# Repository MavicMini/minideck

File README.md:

# MiniDeck  

MiniDeck is a macropad that I have designed to have a lot of functionality in a fairly small package. I wanted to build in the ability to expand its functionalty from just being a macropad to a device which can be used to control smart home devices as well.  

## Features
- 11 Mechanical Switches
- EC11 rotary encoder with push button
- 0.91" 128x32 OLED display
- Sleek case with M3 heat set inserts

## To Do
- ✅ PCB design
- ✅ Case Design
- ✅ Basic KMK firmware
- ❌ Expanded KMK Firmware
- ❌ QMK firmware
- ❌ HomeAssistant integration

## Renders

## CAD Model
All parts are attatches with M3x6mm bolts to make it simple and they screw into 6 M3x4mm heatset inserts. This allows the PCB to be held down with 2 bolts and the case lid 4 bolts.  

The case is printed in two parts, the base and the lid.  

To have the logo stand out I want to have the logo and text be white, my printer only does one colour at a time though. So to achieve the two tone design I need to add a layer pause in the slicer to allow me to change filament during this point and then let it print the last 2 layers of text in white filament.

## PCB
Here is the schematic for the PCB, which were both made in KiCAD. The silkscreen logo was made in Adobe Illustrator.  
**PCB**  

**Schematic**  

## Firmware  
I am going to use KMK firmware to start off with as im more familiar with python so it should be easier to write. However, from the research I've done there are definetly benefits to using QMK, so in the future I might release a QMK firmware version as well.  

Below is a list of the features are currently in the firmware:  
- Rotary encoder changes master system volume
- OLED Displays current volume (Only Works if the volume is exclsivley changed from the MiniDeck)
- 11 Mechanical keys are macros

I plan to add more features and use some keys as modifer keys to extend the functionality of the MiniDeck.

## BOM  
- 11x Cherry MX Switches
- 11x DSA Keycaps
- 6x M3x4mm Heatset Inserts
- 6x M3*6mm Bolts
- 12x 1N4148 Diodes
- 1x 0.91" 128x32 OLED Display
- 1x EC11 Rotary Encoder
- 1x XIAO RP2040
- 1x Top Cover (3D Printed)
- 1x Bottom Case (3D Printed)

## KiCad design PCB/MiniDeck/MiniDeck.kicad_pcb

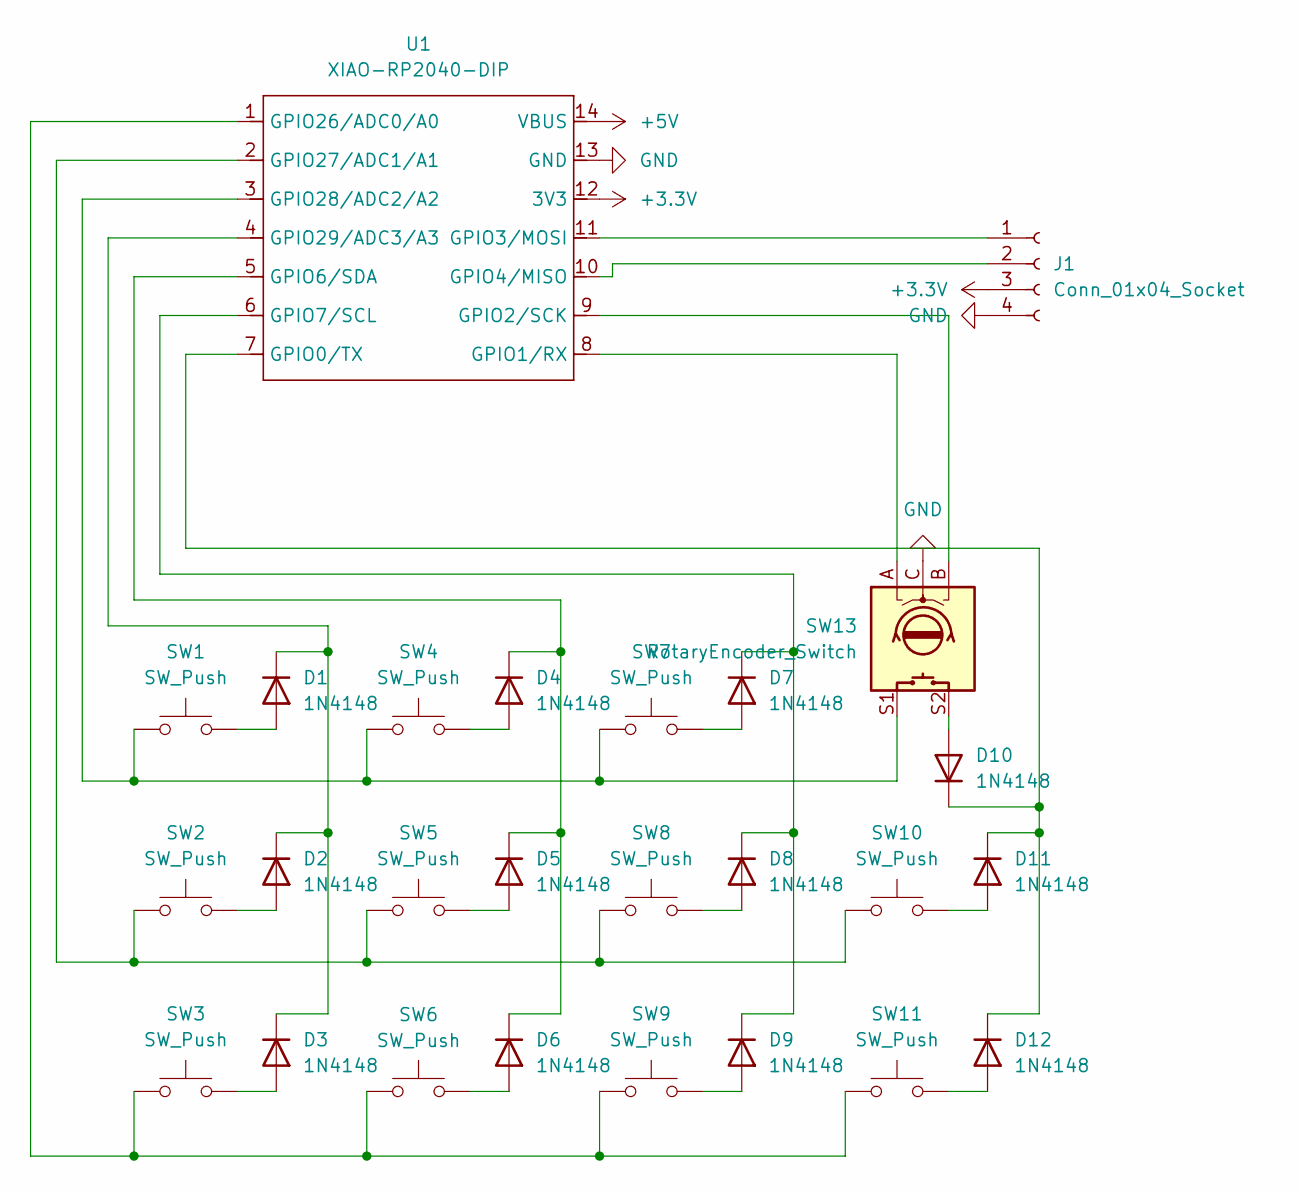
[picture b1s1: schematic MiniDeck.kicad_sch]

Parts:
D1, D2, D3, D4, D5, D6, D7, D8, D9, D10, D11, D12: 1N4148; D_DO-35_SOD27_P7.62mm_Horizontal
J1: Conn_01x04_Socket; PinHeader_1x04_P2.54mm-ce12909e-c1ba-0606-2421-5b6e827065f4
SW1, SW2, SW3, SW4, SW5, SW6, SW7, SW8, SW9, SW10, SW11: SW_Push; SW_Cherry_MX_1.00u_PCB-3D Model
SW13: RotaryEncoder_Switch; RotaryEncoder_Alps_EC11E-Switch_Vertical_H20mm
U1: XIAO-RP2040-DIP

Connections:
+3.3V: J1.3, U1.12 (3V3)
+5V: U1.14 (VBUS)
GND: J1.4, SW13.C, U1.13 (GND)
unnamed: D1.2 (A), SW1.2
unnamed: D1.1 (K), D2.1 (K), D3.1 (K), U1.4 (GPIO29/ADC3/A3)
unnamed: D2.2 (A), SW2.2
unnamed: D3.2 (A), SW3.2
unnamed: D4.2 (A), SW4.2
unnamed: D4.1 (K), D5.1 (K), D6.1 (K), U1.5 (GPIO6/SDA)
unnamed: D5.2 (A), SW5.2
unnamed: D6.2 (A), SW6.2
unnamed: D7.2 (A), SW7.2
unnamed: D7.1 (K), D8.1 (K), D9.1 (K), U1.6 (GPIO7/SCL)
unnamed: D8.2 (A), SW8.2
unnamed: D9.2 (A), SW9.2
unnamed: D10.2 (A), SW13.S2
unnamed: D10.1 (K), D11.1 (K), D12.1 (K), U1.7 (GPIO0/TX)
unnamed: D11.2 (A), SW10.2
unnamed: D12.2 (A), SW11.2
unnamed: J1.1, U1.11 (GPIO3/MOSI)
unnamed: J1.2, U1.10 (GPIO4/MISO)
unnamed: SW13.A, U1.8 (GPIO1/RX)
unnamed: SW13.B, U1.9 (GPIO2/SCK)
unnamed: SW3.1, SW6.1, SW9.1, SW11.1, U1.1 (GPIO26/ADC0/A0)
unnamed: SW2.1, SW5.1, SW8.1, SW10.1, U1.2 (GPIO27/ADC1/A1)
unnamed: SW1.1, SW4.1, SW7.1, SW13.S1, U1.3 (GPIO28/ADC2/A2)

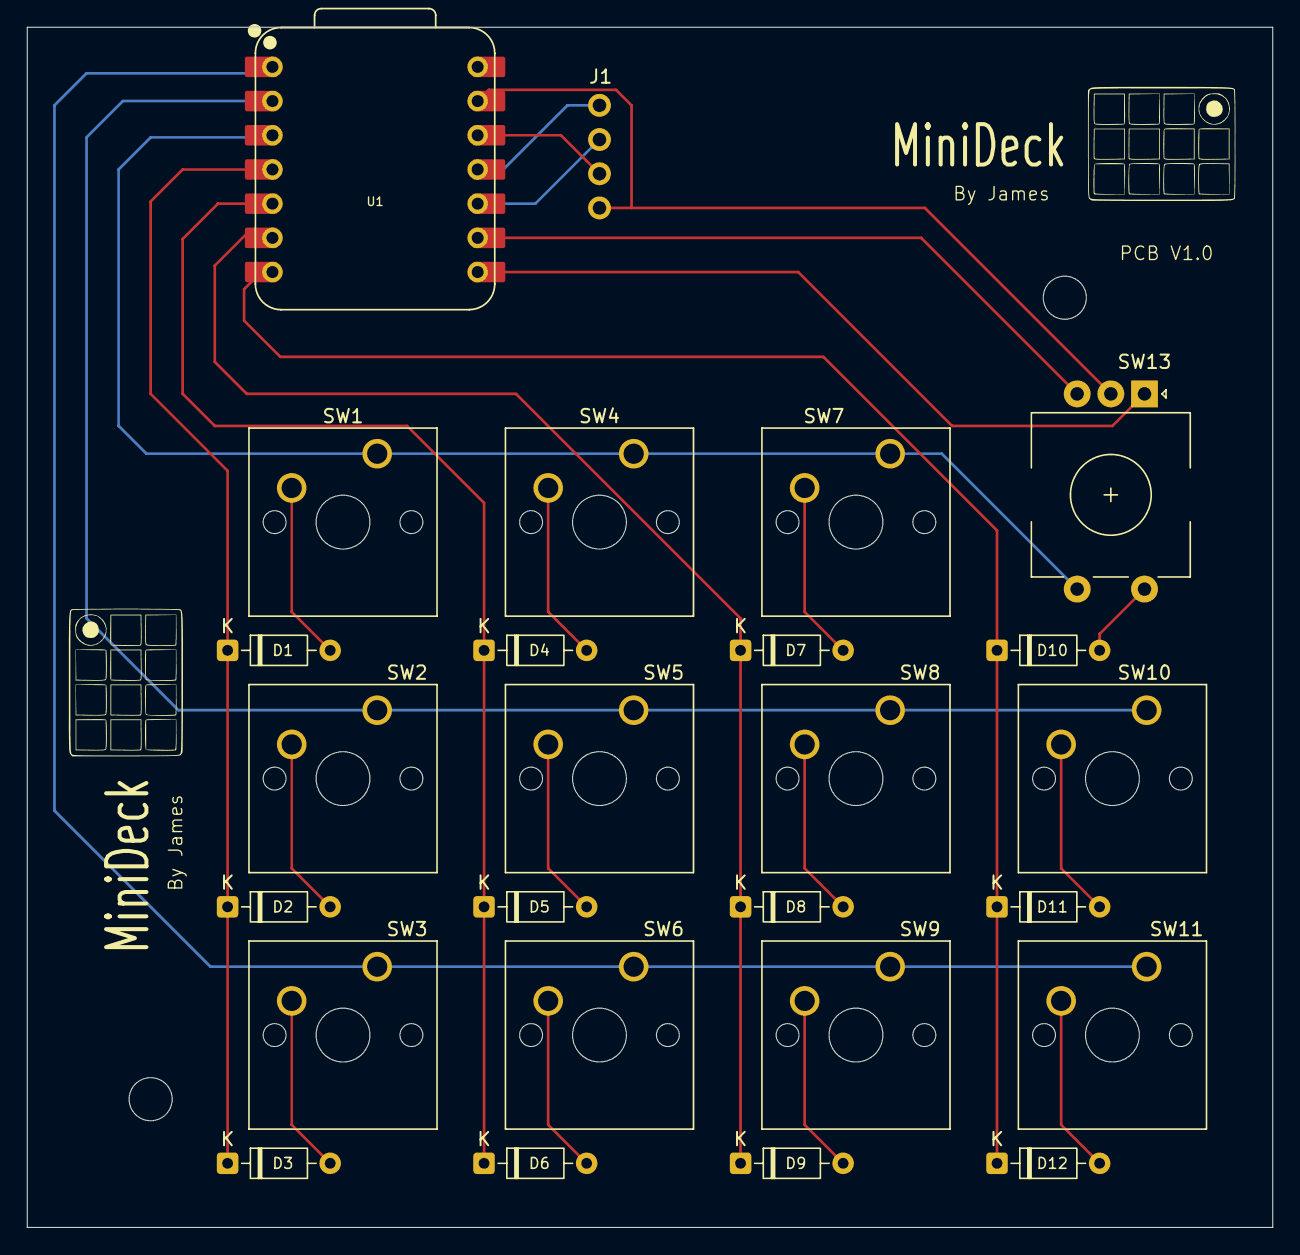
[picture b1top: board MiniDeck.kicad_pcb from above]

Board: 2 copper layers, 92.5 x 89.1 mm, 26 parts (0 on the bottom side), 25 nets.

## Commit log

2025-12-23 Initial folder structure and Images
2025-12-23 Added Logo and Banner Images
2025-12-23 Rename MiniDeck Banner.png to MiniDeck-Banner.png
2025-12-24 Added all main files needed
2025-12-24 Added .gitignore to PCB Folder
2025-12-24 Removed clutter from PCB Folder
2025-12-24 Added render images and screenshots
2025-12-24 Added basic KMK firmware
